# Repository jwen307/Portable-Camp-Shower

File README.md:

# Portable-Camp-Shower
A camping shower with heating element and motorized pump, designed to allow a 7 minute shower with 1 gallon of water. PCB, microcontroller programming, component selection, and 3D printed lid designed from the ground up

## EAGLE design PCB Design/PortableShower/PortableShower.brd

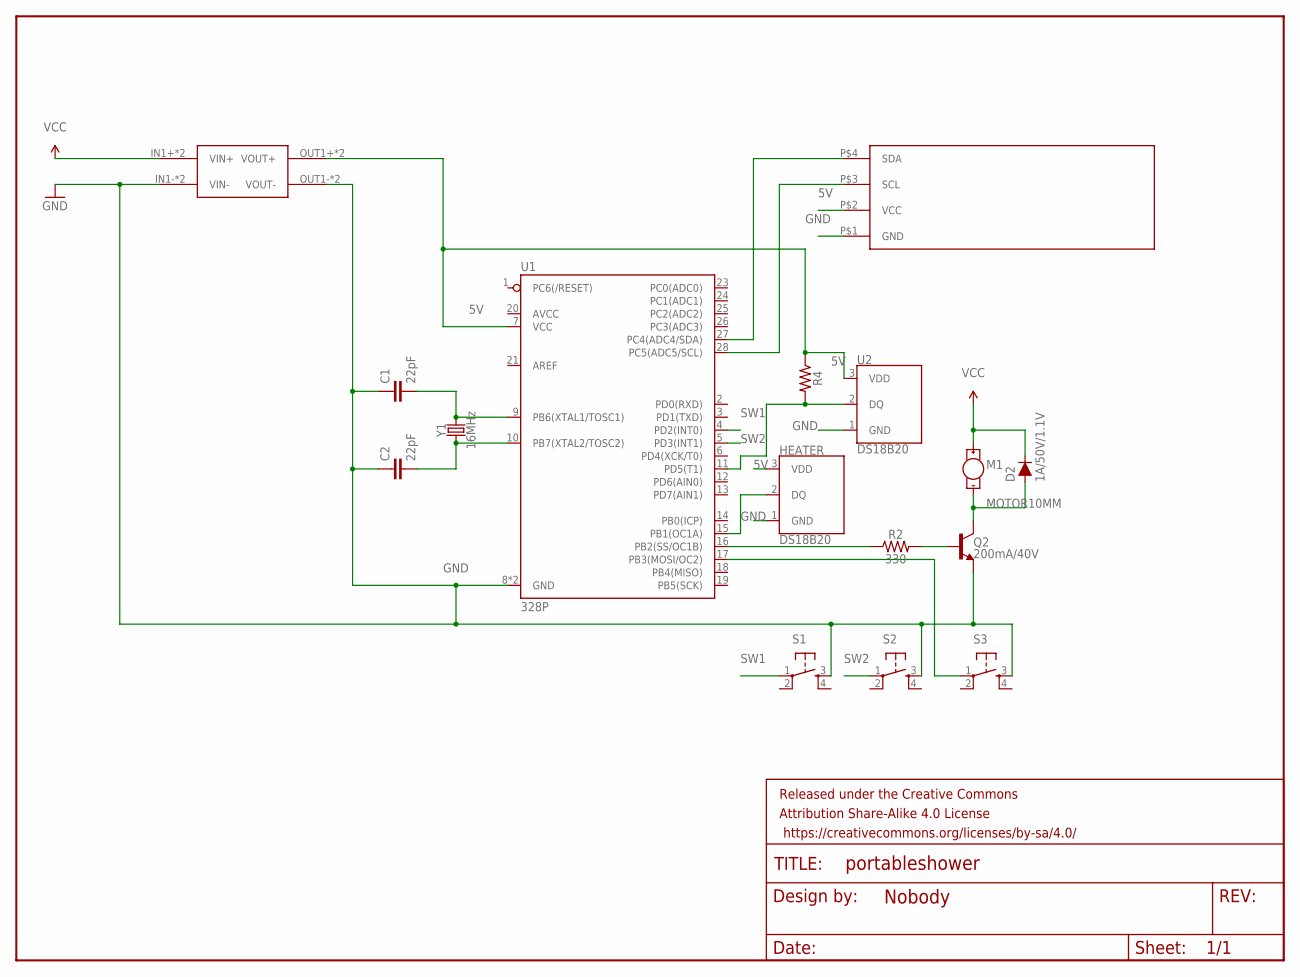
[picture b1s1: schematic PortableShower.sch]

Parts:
C1, C2: 22pF; CAP-PTH-2.54
D2: 1A/50V/1.1V; DIODE-1N4001
FRAME1: FRAME-LETTERNO_PACKAGE; DUMMY
HEATER: DS18B20; TO-92-AMMO
M1: MOTOR10MM; VIBE-MOTOR-10MM
OLED: OLED; SIP
Q2: 200mA/40V; TO-92
R2: 330; AXIAL-0.3
R4: AXIAL-0.3
S1, S2, S3: TAC_SWITCHPTH; TACTILE-PTH
U1: 328P; DIP28
U2: DS18B20; TO-92-AMMO
U$1: MP1584; DC-BRICK
Y1: 16MHz; HC49US

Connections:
5V: HEATER.3 (VDD), OLED.P$2 (VCC), R4.P$1 (1), U1.7 (VCC), U2.3 (VDD), U$1.OUT1+ (VOUT+), U$1.OUT2+ (VOUT+)
GND: C1.1, C2.1, HEATER.1 (GND), OLED.P$1 (GND), Q2.1 (E), S1.3, S2.3, S3.3, U1.8 (GND), U1.22 (GND), U2.1 (GND), U$1.IN1- (VIN-), U$1.IN2- (VIN-), U$1.OUT1- (VOUT-), U$1.OUT2- (VOUT-)
unnamed: C1.2, U1.9 (PB6(XTAL1/TOSC1)), Y1.2
unnamed: C2.2, U1.10 (PB7(XTAL2/TOSC2)), Y1.1
unnamed: OLED.P$4 (SDA), U1.27 (PC4(ADC4/SDA))
unnamed: OLED.P$3 (SCL), U1.28 (PC5(ADC5/SCL))
unnamed: R2.P$1 (1), U1.16 (PB2(SS/OC1B))
unnamed: Q2.2 (B), R2.P$2 (2)
unnamed: D2.A, M1.-, Q2.3 (C)
unnamed: R4.P$2 (2), U1.11 (PD5(T1)), U2.2 (DQ)
unnamed: HEATER.2 (DQ), U1.15 (PB1(OC1A))
unnamed: S3.1, U1.17 (PB3(MOSI/OC2))
SW1: S1.1, U1.4 (PD2(INT0))
SW2: S2.1, U1.5 (PD3(INT1))
VCC: D2.C, M1.+, U$1.IN1+ (VIN+), U$1.IN2+ (VIN+)

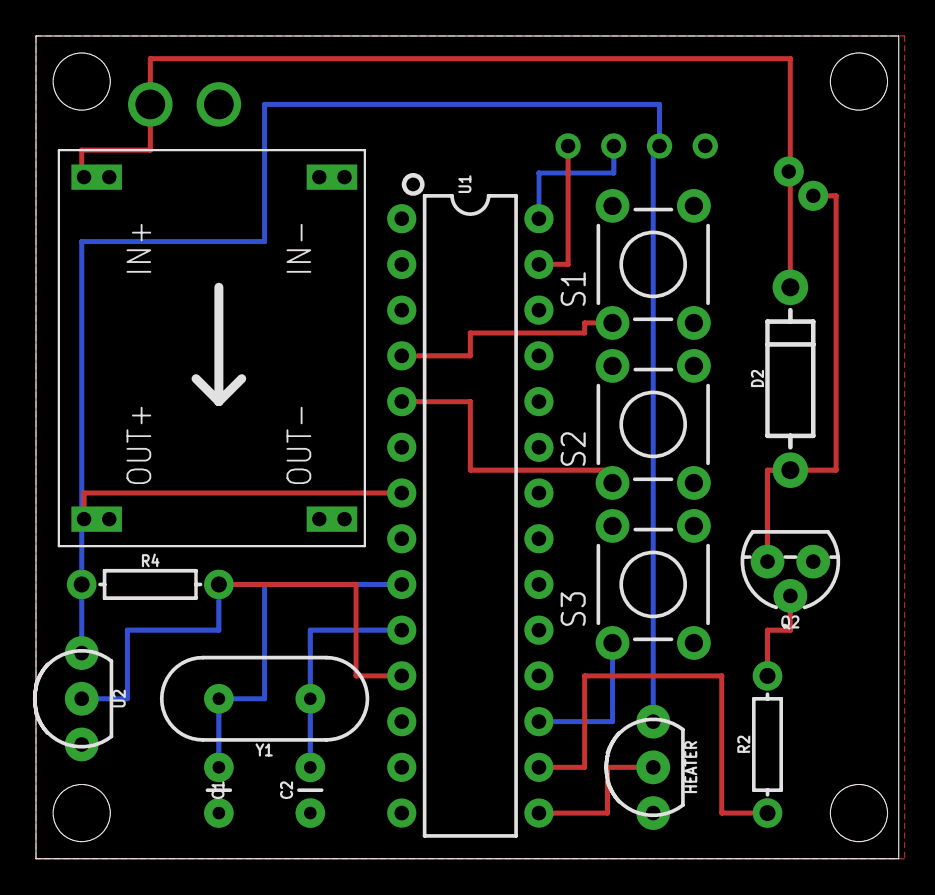
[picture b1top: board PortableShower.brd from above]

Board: 2 copper layers, 47.9 x 45.7 mm, 17 parts (1 on the bottom side), 15 nets.

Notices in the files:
parts and their libraries:
SparkFun-Capacitors: Licensing: Creative Commons ShareAlike 4.0 International - https://creativecommons.org/licenses/by-sa/4.0
SparkFun-Aesthetics: Released under the Creative Commons Attribution Share-Alike 4.0 License
SparkFun-Aesthetics: https://creativecommons.org/licenses/by-sa/4.0
